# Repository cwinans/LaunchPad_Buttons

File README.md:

LaunchPad_Buttons
=================

Basic booster pack  containing directional buttons and some LEDs for a TI launchpad

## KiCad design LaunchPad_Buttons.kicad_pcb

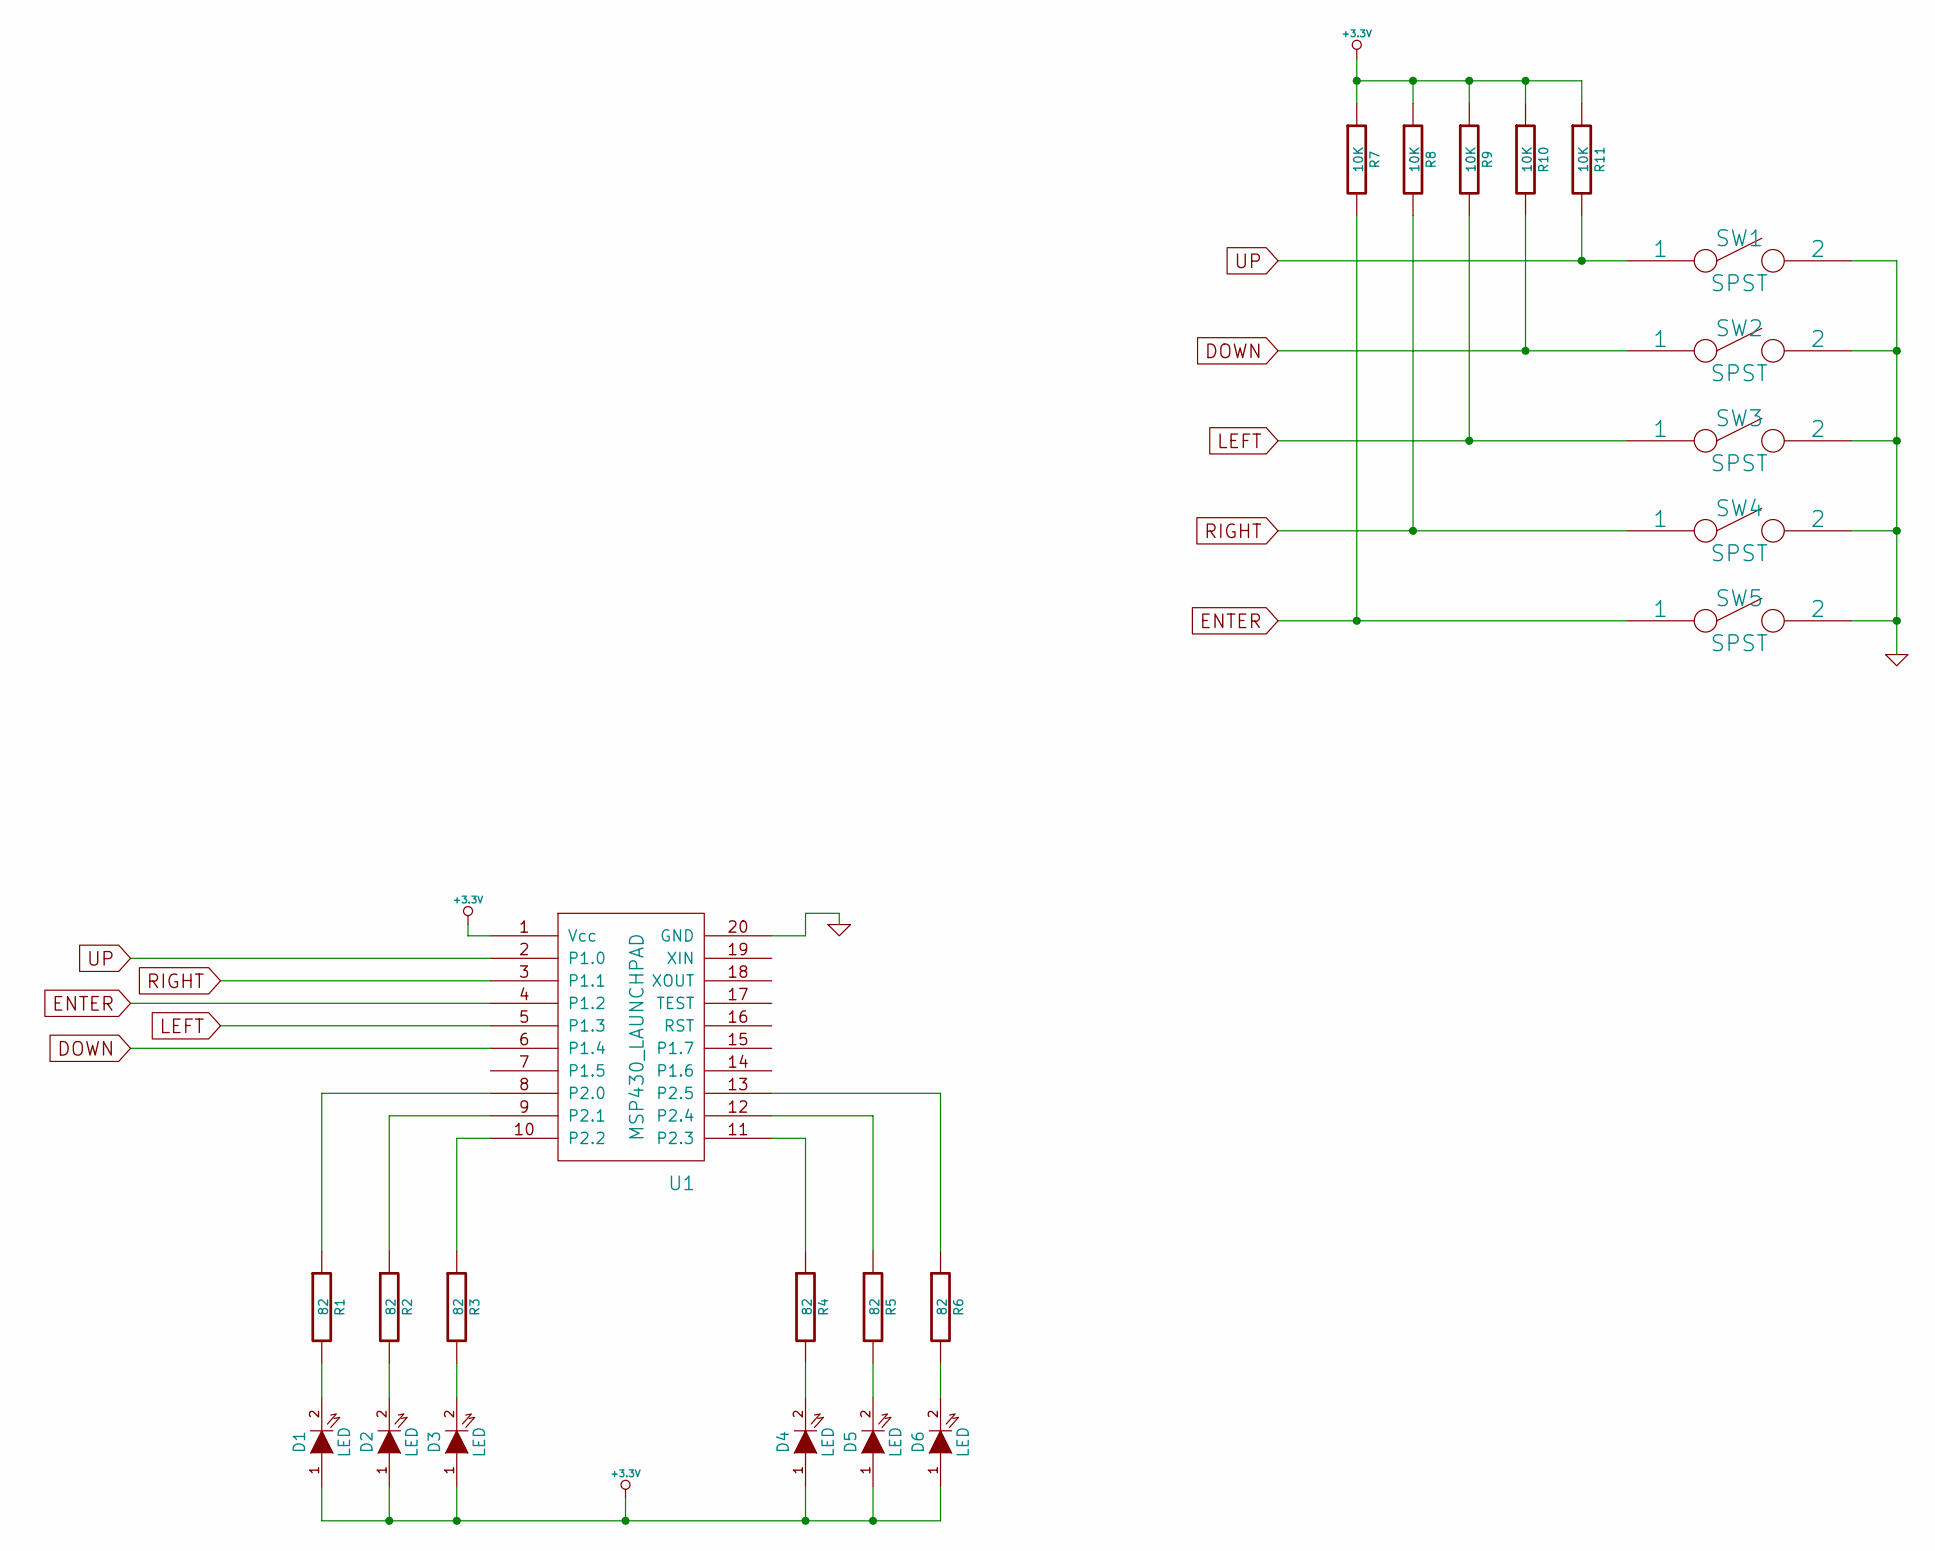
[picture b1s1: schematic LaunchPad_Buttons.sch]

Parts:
D1, D2, D3, D4, D5, D6: LED
R1, R2, R3, R4, R5, R6: 82
R7, R8, R9, R10, R11: 10K
SW1, SW2, SW3, SW4, SW5: SPST
U1: MSP430_LAUNCHPAD

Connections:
+3.3V: D1.1 (A), D2.1 (A), D3.1 (A), D4.1 (A), D5.1 (A), D6.1 (A), R7.1, R8.1, R9.1, R10.1, R11.1, U1.1 (Vcc)
DOWN: R10.2, SW2.1, U1.6 (P1.4)
ENTER: R7.2, SW5.1, U1.4 (P1.2)
GND: SW1.2, SW2.2, SW3.2, SW4.2, SW5.2, U1.20 (GND)
LEFT: R9.2, SW3.1, U1.5 (P1.3)
unnamed: R5.1, U1.12 (P2.4)
unnamed: D6.2 (K), R6.2
unnamed: R3.1, U1.10 (P2.2)
unnamed: R2.1, U1.9 (P2.1)
unnamed: R1.1, U1.8 (P2.0)
unnamed: R4.1, U1.11 (P2.3)
unnamed: D5.2 (K), R5.2
unnamed: R6.1, U1.13 (P2.5)
unnamed: D3.2 (K), R3.2
unnamed: D2.2 (K), R2.2
unnamed: D1.2 (K), R1.2
unnamed: D4.2 (K), R4.2
RIGHT: R8.2, SW4.1, U1.3 (P1.1)
UP: R11.2, SW1.1, U1.2 (P1.0)

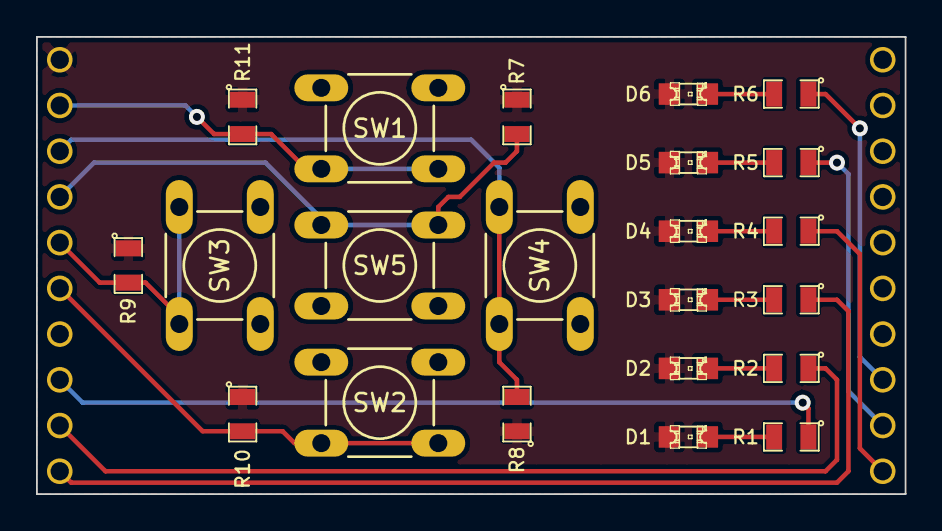
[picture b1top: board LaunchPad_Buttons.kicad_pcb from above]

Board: 2 copper layers, 48.3 x 25.4 mm, 23 parts (0 on the bottom side), 19 nets.

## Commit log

2014-01-29 Launchpad buttons booster pack
    Basic booster pack containing directional buttons and some LEDs for a
    TI launchpad
